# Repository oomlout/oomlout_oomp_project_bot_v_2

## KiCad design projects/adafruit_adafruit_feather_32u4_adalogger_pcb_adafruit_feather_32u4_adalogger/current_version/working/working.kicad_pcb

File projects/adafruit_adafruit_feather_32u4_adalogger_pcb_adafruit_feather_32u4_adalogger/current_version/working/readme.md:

# adafruit_feather_32u4_adalogger_pcb
 
## summary 
* id: adafruit_adafruit_feather_32u4_adalogger_pcb_adafruit_feather_32u4_adalogger
* user: adafruit
* name: adafruit_feather_32u4_adalogger_pcb
* board: adafruit_feather_32u4_adalogger
* repo: https://github.com/adafruit/Adafruit-Feather-32u4-Adalogger-PCB

* src_file_repo_sch: 
* src_file_repo_sch_link: https://github.com/adafruit/Adafruit-Feather-32u4-Adalogger-PCB/tree/master/
* full details link: https://github.com/oomlout/oomlout_oomp_project_bot_v_2/tree/main/projects/adafruit_adafruit_feather_32u4_adalogger_pcb_adafruit_feather_32u4_adalogger/current_version/working  

## schematic  
  
[schematic (pdf)](working_schematic.pdf) 

## pcb  

[board (pdf)](working.pdf)  

## working_bom
| Id | Designator | Footprint | Quantity | Designation | Supplier and ref |  | None | 
| --- | --- | --- | --- | --- | --- | --- | --- | 
| 1 | U$35,U$34 | FIDUCIAL_1MM | 2 | FIDUCIAL" |  |  | [''] | 
| 2 | U3 | SOT23-5 | 1 | MCP73831T-2ACI/OT |  |  | [''] | 
| 3 | U$32,U$31 | MOUNTINGHOLE_2.5_PLATED | 2 | MOUNTINGHOLE2.5 |  |  | [''] | 
| 4 | C7,C14 | 0603-NO | 2 | 1uF |  |  | [''] | 
| 5 | IC1 | TQFN44_7MM | 1 | ATMEGA32U4-MU |  |  | [''] | 
| 6 | C8,C3,C6 | 0805-NO | 3 | 10ÂµF |  |  | [''] | 
| 7 | R8 | 0603-NO | 1 | 10K\ |  |  | [''] | 
| 8 | X1 | JSTPH2 | 1 | JSTPH |  |  | [''] | 
| 9 | R5,R4 | 0603-NO | 2 | 22 |  |  | [''] | 
| 10 | R3,R9 | 0603-NO | 2 | 100k |  |  | [''] | 
| 11 | JP1 | 1X16_ROUND | 1 |  |  |  | [''] | 
| 12 | U$5 | PCBFEAT-REV-040 | 1 |  |  |  | [''] | 
| 13 | C9 | 0805-NO | 1 | 10uF |  |  | [''] | 
| 14 | @HOLE1,@HOLE0 |  | 2 |  |  |  | [''] | 
| 15 | JP3 | 1X12_ROUND | 1 |  |  |  | [''] | 
| 16 | U2 | SOT23-5 | 1 | SPX3819-3.3 |  |  | [''] | 
| 17 | X2 | MICROSD | 1 | microsd |  |  | [''] | 
| 18 | L0 | CHIPLED_0805_NOOUTLINE | 1 | RED |  |  | [''] | 
| 19 | D4 | SOD-123 | 1 | MBR120 |  |  | [''] | 
| 20 | SW1 | KMR2 | 1 | SPST_TACT-KMR2 |  |  | [''] | 
| 21 | R1,R2 | 0603-NO | 2 | 1K |  |  | [''] | 
| 22 | X3 | 4UCONN_20329_V2 | 1 | microUSB |  |  | [''] | 
| 23 | L1 | CHIPLED_0805_NOOUTLINE | 1 | GREEN |  |  | [''] | 
| 24 | R7 | 0603-NO | 1 | 2.2K |  |  | [''] | 
| 25 | Y1 | RESONATOR-SMD | 1 | 8MHz |  |  | [''] | 
| 26 | R6 | _0603MP | 1 | 100K |  |  | [''] | 
| 27 | CHG0 | CHIPLED_0805_NOOUTLINE | 1 | ORANGE |  |  | [''] | 
| 28 | U$7 | ADAFRUIT_3.5MM | 1 |  |  |  | [''] | 
| 29 | U$4 | FEATHERLOGO | 1 |  |  |  | [''] | 
| 30 | U$6 | ADALOGGER_LOGO | 1 |  |  |  | [''] | 

## bom_schematic
| Ref | Qnty | Value | Cmp name | Footprint | Description | Vendor | DNP | 
| --- | --- | --- | --- | --- | --- | --- | --- | 
| C3, C6, C8 | 3 | 10ÂµF | CAP_CERAMIC0805-NOOUTLINE | working:0805-NO |  |  |  | 
| C7, C14 | 2 | 1uF | CAP_CERAMIC0603_NO | working:0603-NO |  |  |  | 
| C9 | 1 | 10uF | CAP_CERAMIC0805-NOOUTLINE | working:0805-NO |  |  |  | 
| CHG0 | 1 | ORANGE | LED0805_NOOUTLINE | working:CHIPLED_0805_NOOUTLINE |  |  |  | 
| D4 | 1 | MBR120 | DIODE-SCHOTTKYSOD-123 | working:SOD-123 |  |  |  | 
| IC1 | 1 | ATMEGA32U4-MU | ATMEGA32U4-MU | working:TQFN44_7MM |  |  |  | 
| JP1 | 1 | HEADER-1X16ROUND | HEADER-1X16ROUND | working:1X16_ROUND |  |  |  | 
| JP3 | 1 | HEADER-1X12 | HEADER-1X12 | working:1X12_ROUND |  |  |  | 
| L0 | 1 | RED | LED0805_NOOUTLINE | working:CHIPLED_0805_NOOUTLINE |  |  |  | 
| L1 | 1 | GREEN | LED0805_NOOUTLINE | working:CHIPLED_0805_NOOUTLINE |  |  |  | 
| R1, R2 | 2 | 1K | RESISTOR_0603_NOOUT | working:0603-NO |  |  |  | 
| R3, R9 | 2 | 100k | RESISTOR_0603_NOOUT | working:0603-NO |  |  |  | 
| R4, R5 | 2 | 22 | RESISTOR_0603_NOOUT | working:0603-NO |  |  |  | 
| R6 | 1 | 100K | RESISTOR_0603MP | working:_0603MP |  |  |  | 
| R7 | 1 | 2.2K | RESISTOR_0603_NOOUT | working:0603-NO |  |  |  | 
| R8 | 1 | 10K\ | RESISTOR_0603_NOOUT | working:0603-NO |  |  |  | 
| SW1 | 1 | SPST_TACT-KMR2 | SPST_TACT-KMR2 | working:KMR2 |  |  |  | 
| U2 | 1 | SPX3819-3.3 | VREG_SOT23-5 | working:SOT23-5 |  |  |  | 
| U3 | 1 | MCP73831T-2ACI/OT | MCP73831/2 | working:SOT23-5 |  |  |  | 
| U$31, U$32 | 2 | MOUNTINGHOLE2.5 | MOUNTINGHOLE2.5 | working:MOUNTINGHOLE_2.5_PLATED |  |  |  | 
| U$34, U$35 | 2 | FIDUCIAL"" | FIDUCIAL{dblquote}{dblquote} | working:FIDUCIAL_1MM |  |  |  | 
| X1 | 1 | JSTPH | CON_JST_PH_2PIN | working:JSTPH2 |  |  |  | 
| X2 | 1 | microsd | MICROSD | working:MICROSD |  |  |  | 
| X3 | 1 | microUSB | USB_MICRO_20329_V2 | working:4UCONN_20329_V2 |  |  |  | 
| Y1 | 1 | RESONATORSMD | RESONATORSMD | working:RESONATOR-SMD |  |  |  | 

## mounting_holes
| x | y | package | value | ref | size | 
| --- | --- | --- | --- | --- | --- | 
| 0.0 | 17.78 | MOUNTINGHOLE_2.5_PLATED | MOUNTINGHOLE2.5 | U$31 | m3 | 
| 0.0 | 0.0 | MOUNTINGHOLE_2.5_PLATED | MOUNTINGHOLE2.5 | U$32 | m3 |

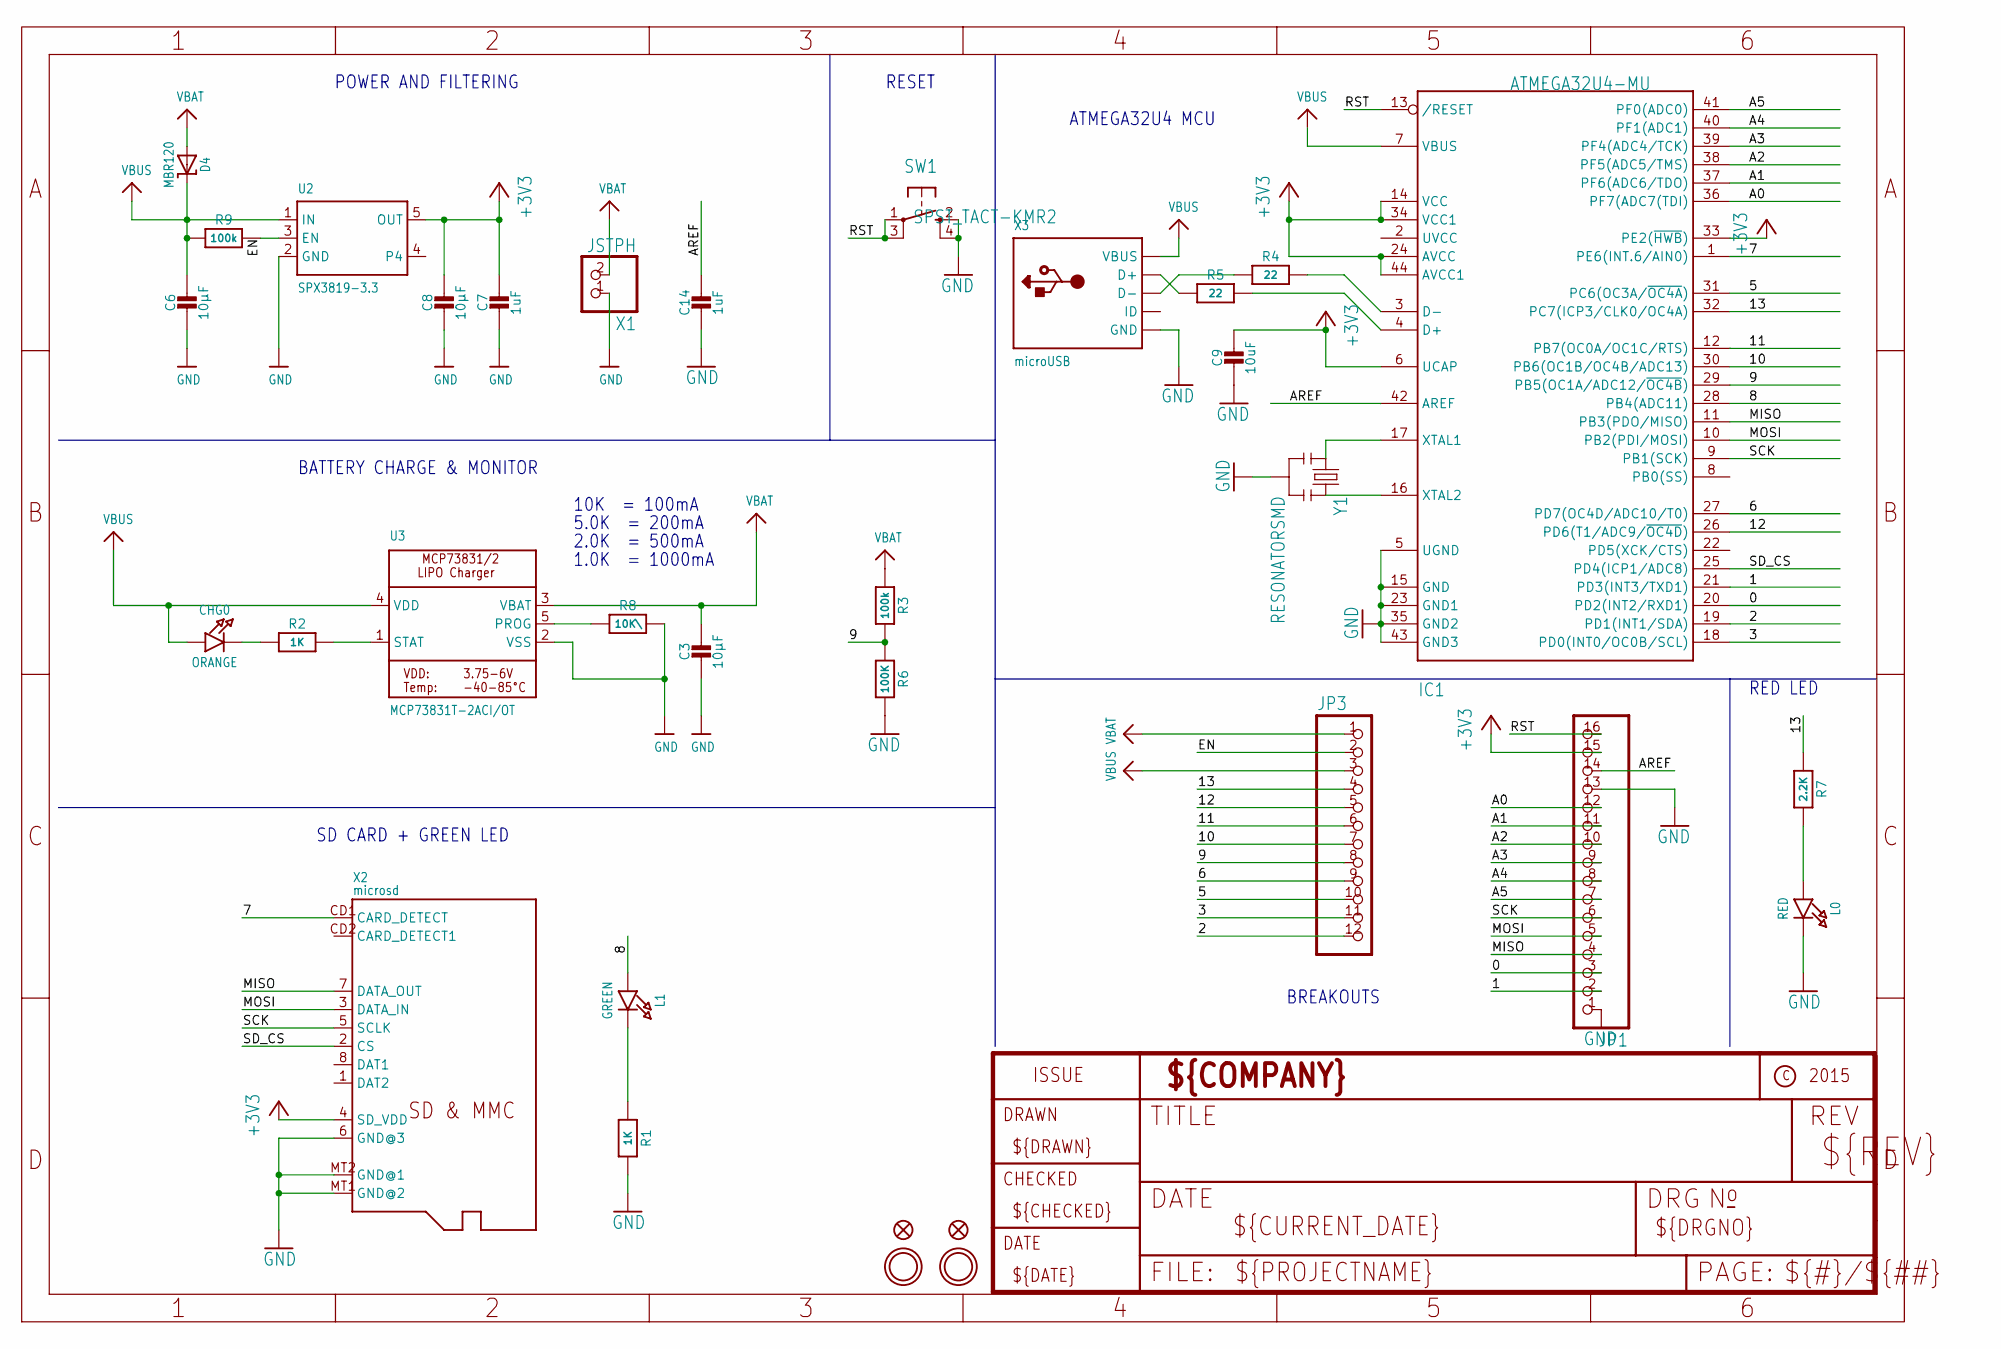
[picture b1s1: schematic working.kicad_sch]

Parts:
C3, C6, C8: 10µF; 0805-NO
C7, C14: 1uF; 0603-NO
C9: 10uF; 0805-NO
CHG0: ORANGE; CHIPLED_0805_NOOUTLINE
D4: MBR120; SOD-123
IC1: ATMEGA32U4-MU; TQFN44_7MM
JP1: HEADER-1X16ROUND; 1X16_ROUND
JP3: HEADER-1X12; 1X12_ROUND
L0: RED; CHIPLED_0805_NOOUTLINE
L1: GREEN; CHIPLED_0805_NOOUTLINE
R1, R2: 1K; 0603-NO
R3, R9: 100k; 0603-NO
R4, R5: 22; 0603-NO
R6: 100K; _0603MP
R7: 2.2K; 0603-NO
R8: 10K\; 0603-NO
SW1: SPST_TACT-KMR2; KMR2
U2: SPX3819-3.3; SOT23-5
U3: MCP73831T-2ACI/OT; SOT23-5
U$31, U$32: MOUNTINGHOLE2.5; MOUNTINGHOLE_2.5_PLATED
U$34, U$35: FIDUCIAL""; FIDUCIAL_1MM
X1: JSTPH; JSTPH2
X2: microsd; MICROSD
X3: microUSB; 4UCONN_20329_V2
Y1: RESONATORSMD; RESONATOR-SMD

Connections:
0: IC1.20 (PD2(INT2/RXD1)), JP1.3
1: IC1.21 (PD3(INT3/TXD1)), JP1.2
2: IC1.19 (PD1(INT1/SDA)), JP3.12
3: IC1.18 (PD0(INT0/OC0B/SCL)), JP3.11
5: IC1.31 (PC6(OC3A/~OC4A)), JP3.10
6: IC1.27 (PD7(OC4D/ADC10/T0)), JP3.9
7: IC1.1 (PE6(INT.6/AIN0)), X2.CD1 (CARD_DETECT)
8: IC1.28 (PB4(ADC11)), L1.A
9: IC1.29 (PB5(OC1A/ADC12/~OC4B)), JP3.8, R3.2, R6.1
10: IC1.30 (PB6(OC1B/OC4B/ADC13)), JP3.7
11: IC1.12 (PB7(OC0A/OC1C/RTS)), JP3.6
12: IC1.26 (PD6(T1/ADC9/~OC4D)), JP3.5
13: IC1.32 (PC7(ICP3/CLK0/OC4A)), JP3.4, R7.1
+3V3: C7.1, C8.1, C9.1, IC1.6 (UCAP), IC1.14 (VCC), IC1.24 (AVCC), IC1.33 (PE2(~HWB)), IC1.34 (VCC1), IC1.44 (AVCC1), JP1.15, U2.5 (OUT), X2.4 (SD_VDD)
A0: IC1.36 (PF7(ADC7(TDI)), JP1.12
A1: IC1.37 (PF6(ADC6/TDO)), JP1.11
A2: IC1.38 (PF5(ADC5/TMS)), JP1.10
A3: IC1.39 (PF4(ADC4/TCK)), JP1.9
A4: IC1.40 (PF1(ADC1)), JP1.8
A5: IC1.41 (PF0(ADC0)), JP1.7
AREF: C14.1, IC1.42 (AREF), JP1.14
D+: IC1.4 (D+), R5.2
D-: IC1.3 (D-), R4.2
EN: JP3.2, R9.2, U2.3 (EN)
GND: C3.2, C6.2, C7.2, C8.2, C9.2, C14.2, IC1.5 (UGND), IC1.15 (GND), IC1.23 (GND1), IC1.35 (GND2), IC1.43 (GND3), JP1.1, JP1.13, L0.C, R1.2, R6.2, R8.2, SW1.2 (S), SW1.4 (S1), U2.2 (GND), U3.2 (VSS), X1.1, X2.6 (GND@3), X2.MT1 (GND@2), X2.MT2 (GND@1), X3.BASE@1 (GND), X3.BASE@2 (GND), X3.GND, X3.SPRT@1 (GND), X3.SPRT@2 (GND), X3.SPRT@3 (GND), X3.SPRT@4 (GND), Y1.2
MISO: IC1.11 (PB3(PDO/MISO)), JP1.4, X2.7 (DATA_OUT)
MOSI: IC1.10 (PB2(PDI/MOSI)), JP1.5, X2.3 (DATA_IN)
unnamed: CHG0.C, R2.1
unnamed: L0.A, R7.2
unnamed: R2.2, U3.1 (STAT)
unnamed: R8.1, U3.5 (PROG)
unnamed: L1.C, R1.1
unnamed: IC1.16 (XTAL2), Y1.3
unnamed: IC1.17 (XTAL1), Y1.1
unnamed: R5.1, X3.D+
unnamed: R4.1, X3.D-
RST: IC1.13 (/RESET), JP1.16, SW1.1, SW1.3 (P1)
SCK: IC1.9 (PB1(SCK)), JP1.6, X2.5 (SCLK)
SD_CS: IC1.25 (PD4(ICP1/ADC8)), X2.2 (CS)
VBAT: C3.1, D4.A, JP3.1, R3.1, U3.3 (VBAT), X1.2
VBUS: C6.1, CHG0.A, D4.C, IC1.7 (VBUS), JP3.3, R9.1, U2.1 (IN), U3.4 (VDD), X3.VBUS

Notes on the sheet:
10K = 100mA
RESET
5.0K = 200mA
BATTERY CHARGE & MONITOR
2.0K = 500mA
SD CARD + GREEN LED
ATMEGA32U4 MCU
1.0K = 1000mA
POWER AND FILTERING
BREAKOUTS
RED LED

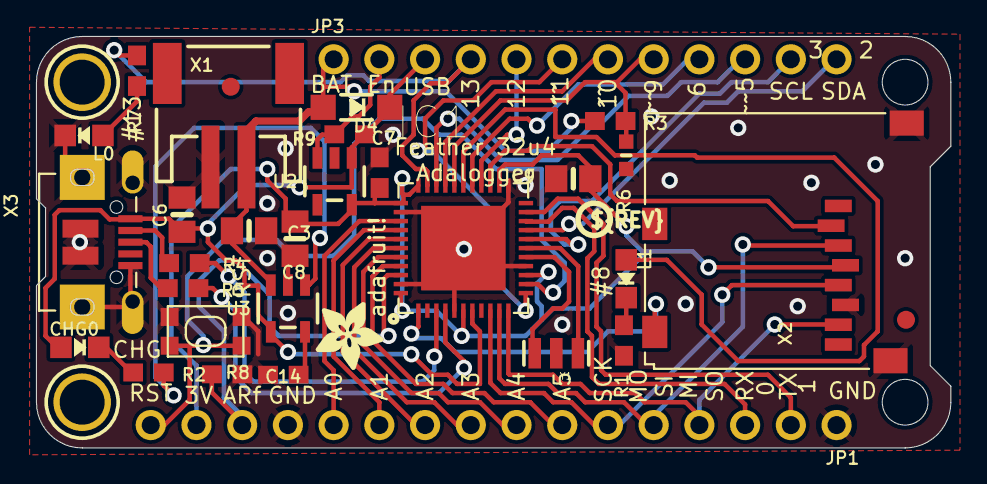
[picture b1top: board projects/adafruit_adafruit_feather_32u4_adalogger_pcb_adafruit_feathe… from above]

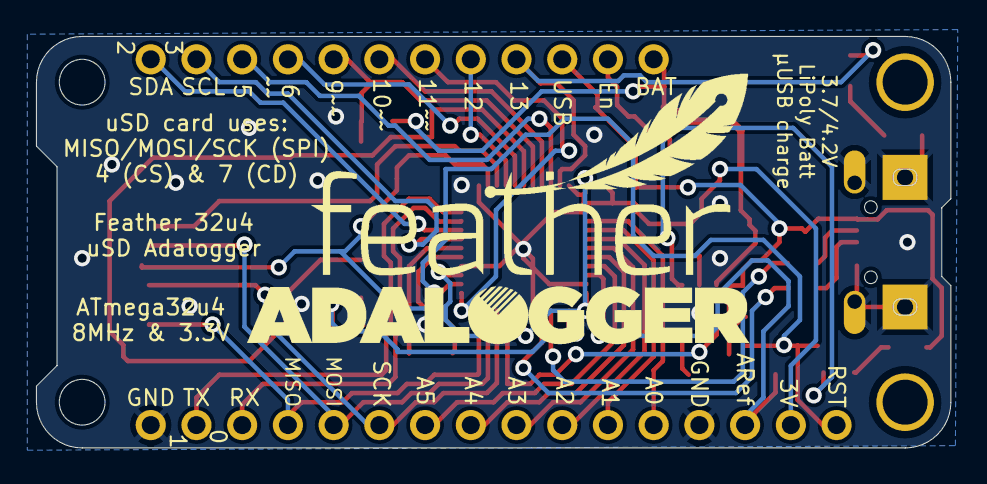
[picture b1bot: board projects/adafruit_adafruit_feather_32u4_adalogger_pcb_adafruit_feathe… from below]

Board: 2 copper layers, 50.8 x 22.9 mm, 39 parts (2 on the bottom side), 41 nets.

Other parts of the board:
@HOLE0, @HOLE1: (no value)
U$4: FEATHERLOGO
U$5: PCBFEAT-REV-040
U$6: ADALOGGER_LOGO
U$7: ADAFRUIT_3.5MM

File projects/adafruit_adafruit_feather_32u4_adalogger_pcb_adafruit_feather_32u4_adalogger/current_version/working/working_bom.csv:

"Id";"Designator";"Footprint";"Quantity";"Designation";"Supplier and ref";
1;"U$35,U$34";"FIDUCIAL_1MM";2;"FIDUCIAL""";;;
2;"U3";"SOT23-5";1;"MCP73831T-2ACI/OT";;;
3;"U$32,U$31";"MOUNTINGHOLE_2.5_PLATED";2;"MOUNTINGHOLE2.5";;;
4;"C7,C14";"0603-NO";2;"1uF";;;
5;"IC1";"TQFN44_7MM";1;"ATMEGA32U4-MU";;;
6;"C8,C3,C6";"0805-NO";3;"10µF";;;
7;"R8";"0603-NO";1;"10K\";;;
8;"X1";"JSTPH2";1;"JSTPH";;;
9;"R5,R4";"0603-NO";2;"22";;;
10;"R3,R9";"0603-NO";2;"100k";;;
11;"JP1";"1X16_ROUND";1;"";;;
12;"U$5";"PCBFEAT-REV-040";1;"";;;
13;"C9";"0805-NO";1;"10uF";;;
14;"@HOLE1,@HOLE0";"";2;"";;;
15;"JP3";"1X12_ROUND";1;"";;;
16;"U2";"SOT23-5";1;"SPX3819-3.3";;;
17;"X2";"MICROSD";1;"microsd";;;
18;"L0";"CHIPLED_0805_NOOUTLINE";1;"RED";;;
19;"D4";"SOD-123";1;"MBR120";;;
20;"SW1";"KMR2";1;"SPST_TACT-KMR2";;;
21;"R1,R2";"0603-NO";2;"1K";;;
22;"X3";"4UCONN_20329_V2";1;"microUSB";;;
23;"L1";"CHIPLED_0805_NOOUTLINE";1;"GREEN";;;
24;"R7";"0603-NO";1;"2.2K";;;
25;"Y1";"RESONATOR-SMD";1;"8MHz";;;
26;"R6";"_0603MP";1;"100K";;;
27;"CHG0";"CHIPLED_0805_NOOUTLINE";1;"ORANGE";;;
28;"U$7";"ADAFRUIT_3.5MM";1;"";;;
29;"U$4";"FEATHERLOGO";1;"";;;
30;"U$6";"ADALOGGER_LOGO";1;"";;;

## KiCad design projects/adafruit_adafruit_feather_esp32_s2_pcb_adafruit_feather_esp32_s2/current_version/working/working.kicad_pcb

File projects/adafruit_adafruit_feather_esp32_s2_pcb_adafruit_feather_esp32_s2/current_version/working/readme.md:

# adafruit_feather_esp32_s2_pcb
 
## summary 
* id: adafruit_adafruit_feather_esp32_s2_pcb_adafruit_feather_esp32_s2
* user: adafruit
* name: adafruit_feather_esp32_s2_pcb
* board: adafruit_feather_esp32_s2
* repo: https://github.com/adafruit/Adafruit-Feather-ESP32-S2-PCB

* src_file_repo_sch: 
* src_file_repo_sch_link: https://github.com/adafruit/Adafruit-Feather-ESP32-S2-PCB/tree/main/
* full details link: https://github.com/oomlout/oomlout_oomp_project_bot_v_2/tree/main/projects/adafruit_adafruit_feather_esp32_s2_pcb_adafruit_feather_esp32_s2/current_version/working  

## schematic  
  
[schematic (pdf)](working_schematic.pdf) 

## pcb  

[board (pdf)](working.pdf)  

## working_bom
| Id | Designator | Footprint | Quantity | Designation | Supplier and ref |  | None | 
| --- | --- | --- | --- | --- | --- | --- | --- | 
| 1 | U$35,U$34 | FIDUCIAL_1MM | 2 | FIDUCIAL_1MM |  |  | [''] | 
| 2 | C2,C9,C7,C1 | 0805-NO | 4 | 10uF |  |  | [''] | 
| 3 | C10,C4,C5 | 0603-NO | 3 | 1uF |  |  | [''] | 
| 4 | D4 | SOD-123 | 1 | MBR540 |  |  | [''] | 
| 5 | X3 | USB_C_CUSB31-CFM2AX-01-X | 1 | USB C |  |  | [''] | 
| 6 | R8,R10,R4,R2,R5,R1 | 0603-NO | 6 | 5.1K |  |  | [''] | 
| 7 | Q3 | SOT23-R | 1 | DMG3415U |  |  | [''] | 
| 8 | U4 | BME280 | 1 | BME280 |  |  | [''] | 
| 9 | C8,C3,C6 | 0805-NO | 3 | 10ÂµF |  |  | [''] | 
| 10 | R3 | RESPACK_4X0603 | 1 | 10K |  |  | [''] | 
| 11 | R7,R12 | 0603-NO | 2 | 100K |  |  | [''] | 
| 12 | U$32,U$31 | MOUNTINGHOLE_2.5_PLATED | 2 | MOUNTINGHOLE2.5 |  |  | [''] | 
| 13 | D3 | CHIPLED_0603_NOOUTLINE | 1 | RED |  |  | [''] | 
| 14 | SW2,SW1 | BTN_KMR2_4.6X2.8 | 2 | KMR2 |  |  | [''] | 
| 15 | U3 | SOT23-5 | 1 | MCP73831T-2ACI/OT |  |  | [''] | 
| 16 | R17 | 0603-NO | 1 | 1Meg |  |  | [''] | 
| 17 | CHG0 | CHIPLED_0603_NOOUTLINE | 1 | ORANGE |  |  | [''] | 
| 18 | LED1 | SK6805_1515 | 1 | WS2812B_SK6805_1515 |  |  | [''] | 
| 19 | X1 | JSTPH2_BATT | 1 | JSTPH |  |  | [''] | 
| 20 | U1 | QFN60_ESP32-S2-MINI-1_EXP | 1 | ESP32-S2-MODULE_MINI |  |  | [''] | 
| 21 | JP1 | 1X16_ROUND | 1 |  |  |  | [''] | 
| 22 | CONN1 | JST_SH4_RA | 1 | JST SH |  |  | [''] | 
| 23 | @HOLE1,@HOLE0 |  | 2 |  |  |  | [''] | 
| 24 | JP3 | 1X12_ROUND | 1 |  |  |  | [''] | 
| 25 | IC1 | WLCSP9 | 1 | LC709203F/MH |  |  | [''] | 
| 26 | U2,U5 | SOT23-5 | 2 | AP2112/RT9080-3.3 |  |  | [''] | 
| 27 | C11 | _0805MP | 1 | 10uF |  |  | [''] | 
| 28 | TP1 | TESTPOINT_ROUND_1.5MM_NO | 1 |  |  |  | [''] | 
| 29 | U$53 | STEMMAQT | 1 |  |  |  | [''] | 
| 30 | U$15 | FEATHERLOGO_MED | 1 |  |  |  | [''] | 
| 31 | U$14 | PCBFEAT-REV-040 | 1 |  |  |  | [''] | 

## bom_schematic
| Ref | Qnty | Value | Cmp name | Footprint | Description | Vendor | DNP | 
| --- | --- | --- | --- | --- | --- | --- | --- | 
| C1, C2, C7, C9 | 4 | 10uF | CAP_CERAMIC0805-NOOUTLINE | working:0805-NO |  |  |  | 
| C3, C6, C8 | 3 | 10ÂµF | CAP_CERAMIC0805-NOOUTLINE | working:0805-NO |  |  |  | 
| C4, C5, C10 | 3 | 1uF | CAP_CERAMIC0603_NO | working:0603-NO |  |  |  | 
| C11 | 1 | 10uF | CAP_CERAMIC_0805MP | working:_0805MP |  |  |  | 
| CHG0 | 1 | ORANGE | LED0603_NOOUTLINE | working:CHIPLED_0603_NOOUTLINE |  |  |  | 
| CONN1 | 1 | STEMMA_I2C_QTRA | STEMMA_I2C_QTRA | working:JST_SH4_RA |  |  |  | 
| D3 | 1 | RED | LED0603_NOOUTLINE | working:CHIPLED_0603_NOOUTLINE |  |  |  | 
| D4 | 1 | MBR540 | DIODE-SCHOTTKYSOD-123 | working:SOD-123 |  |  |  | 
| IC1 | 1 | LC709203F/MH | LC709203F/MH | working:WLCSP9 |  |  |  | 
| JP1 | 1 | HEADER-1X16ROUND | HEADER-1X16ROUND | working:1X16_ROUND |  |  |  | 
| JP3 | 1 | HEADER-1X12 | HEADER-1X12 | working:1X12_ROUND |  |  |  | 
| LED1 | 1 | WS2812B_SK6805_1515 | WS2812B_SK6805_1515 | working:SK6805_1515 |  |  |  | 
| Q3 | 1 | DMG3415U | MOSFET-P | working:SOT23-R |  |  |  | 
| R1, R2, R4, R5, R8, R10 | 6 | 5.1K | RESISTOR_0603_NOOUT | working:0603-NO |  |  |  | 
| R3 | 1 | 10K | RESISTOR_4PACK | working:RESPACK_4X0603 |  |  |  | 
| R7, R12 | 2 | 100K | RESISTOR_0603_NOOUT | working:0603-NO |  |  |  | 
| R17 | 1 | 1Meg | RESISTOR_0603_NOOUT | working:0603-NO |  |  |  | 
| SW1, SW2 | 2 | KMR2 | SWITCH_TACT_SMT4.6X2.8 | working:BTN_KMR2_4.6X2.8 |  |  |  | 
| TP1 | 1 | TESTPOINTROUND1.5MMNO | TESTPOINTROUND1.5MMNO | working:TESTPOINT_ROUND_1.5MM_NO |  |  |  | 
| U1 | 1 | ESP32-S2-MODULE_MINI | ESP32-S2-MODULE_MINI | working:QFN60_ESP32-S2-MINI-1_EXP |  |  |  | 
| U2, U5 | 2 | AP2112/RT9080-3.3 | VREG_SOT23-5 | working:SOT23-5 |  |  |  | 
| U3 | 1 | MCP73831T-2ACI/OT | MCP73831/2 | working:SOT23-5 |  |  |  | 
| U4 | 1 | BME280 | BME280 | working:BME280 |  |  |  | 
| U$31, U$32 | 2 | MOUNTINGHOLE2.5 | MOUNTINGHOLE2.5 | working:MOUNTINGHOLE_2.5_PLATED |  |  |  | 
| U$34, U$35 | 2 | FIDUCIAL_1MM | FIDUCIAL_1MM | working:FIDUCIAL_1MM |  |  |  | 
| X1 | 1 | CON_JST_PH_2PIN_MT_BATT | CON_JST_PH_2PIN_MT_BATT | working:JSTPH2_BATT |  |  |  | 
| X3 | 1 | USB C | USB_C | working:USB_C_CUSB31-CFM2AX-01-X |  |  |  | 

## mounting_holes
| x | y | package | value | ref | size | 
| --- | --- | --- | --- | --- | --- | 
| 0.0 | 17.78 | MOUNTINGHOLE_2.5_PLATED | MOUNTINGHOLE2.5 | U$31 | m3 | 
| 0.0 | 0.0 | MOUNTINGHOLE_2.5_PLATED | MOUNTINGHOLE2.5 | U$32 | m3 |

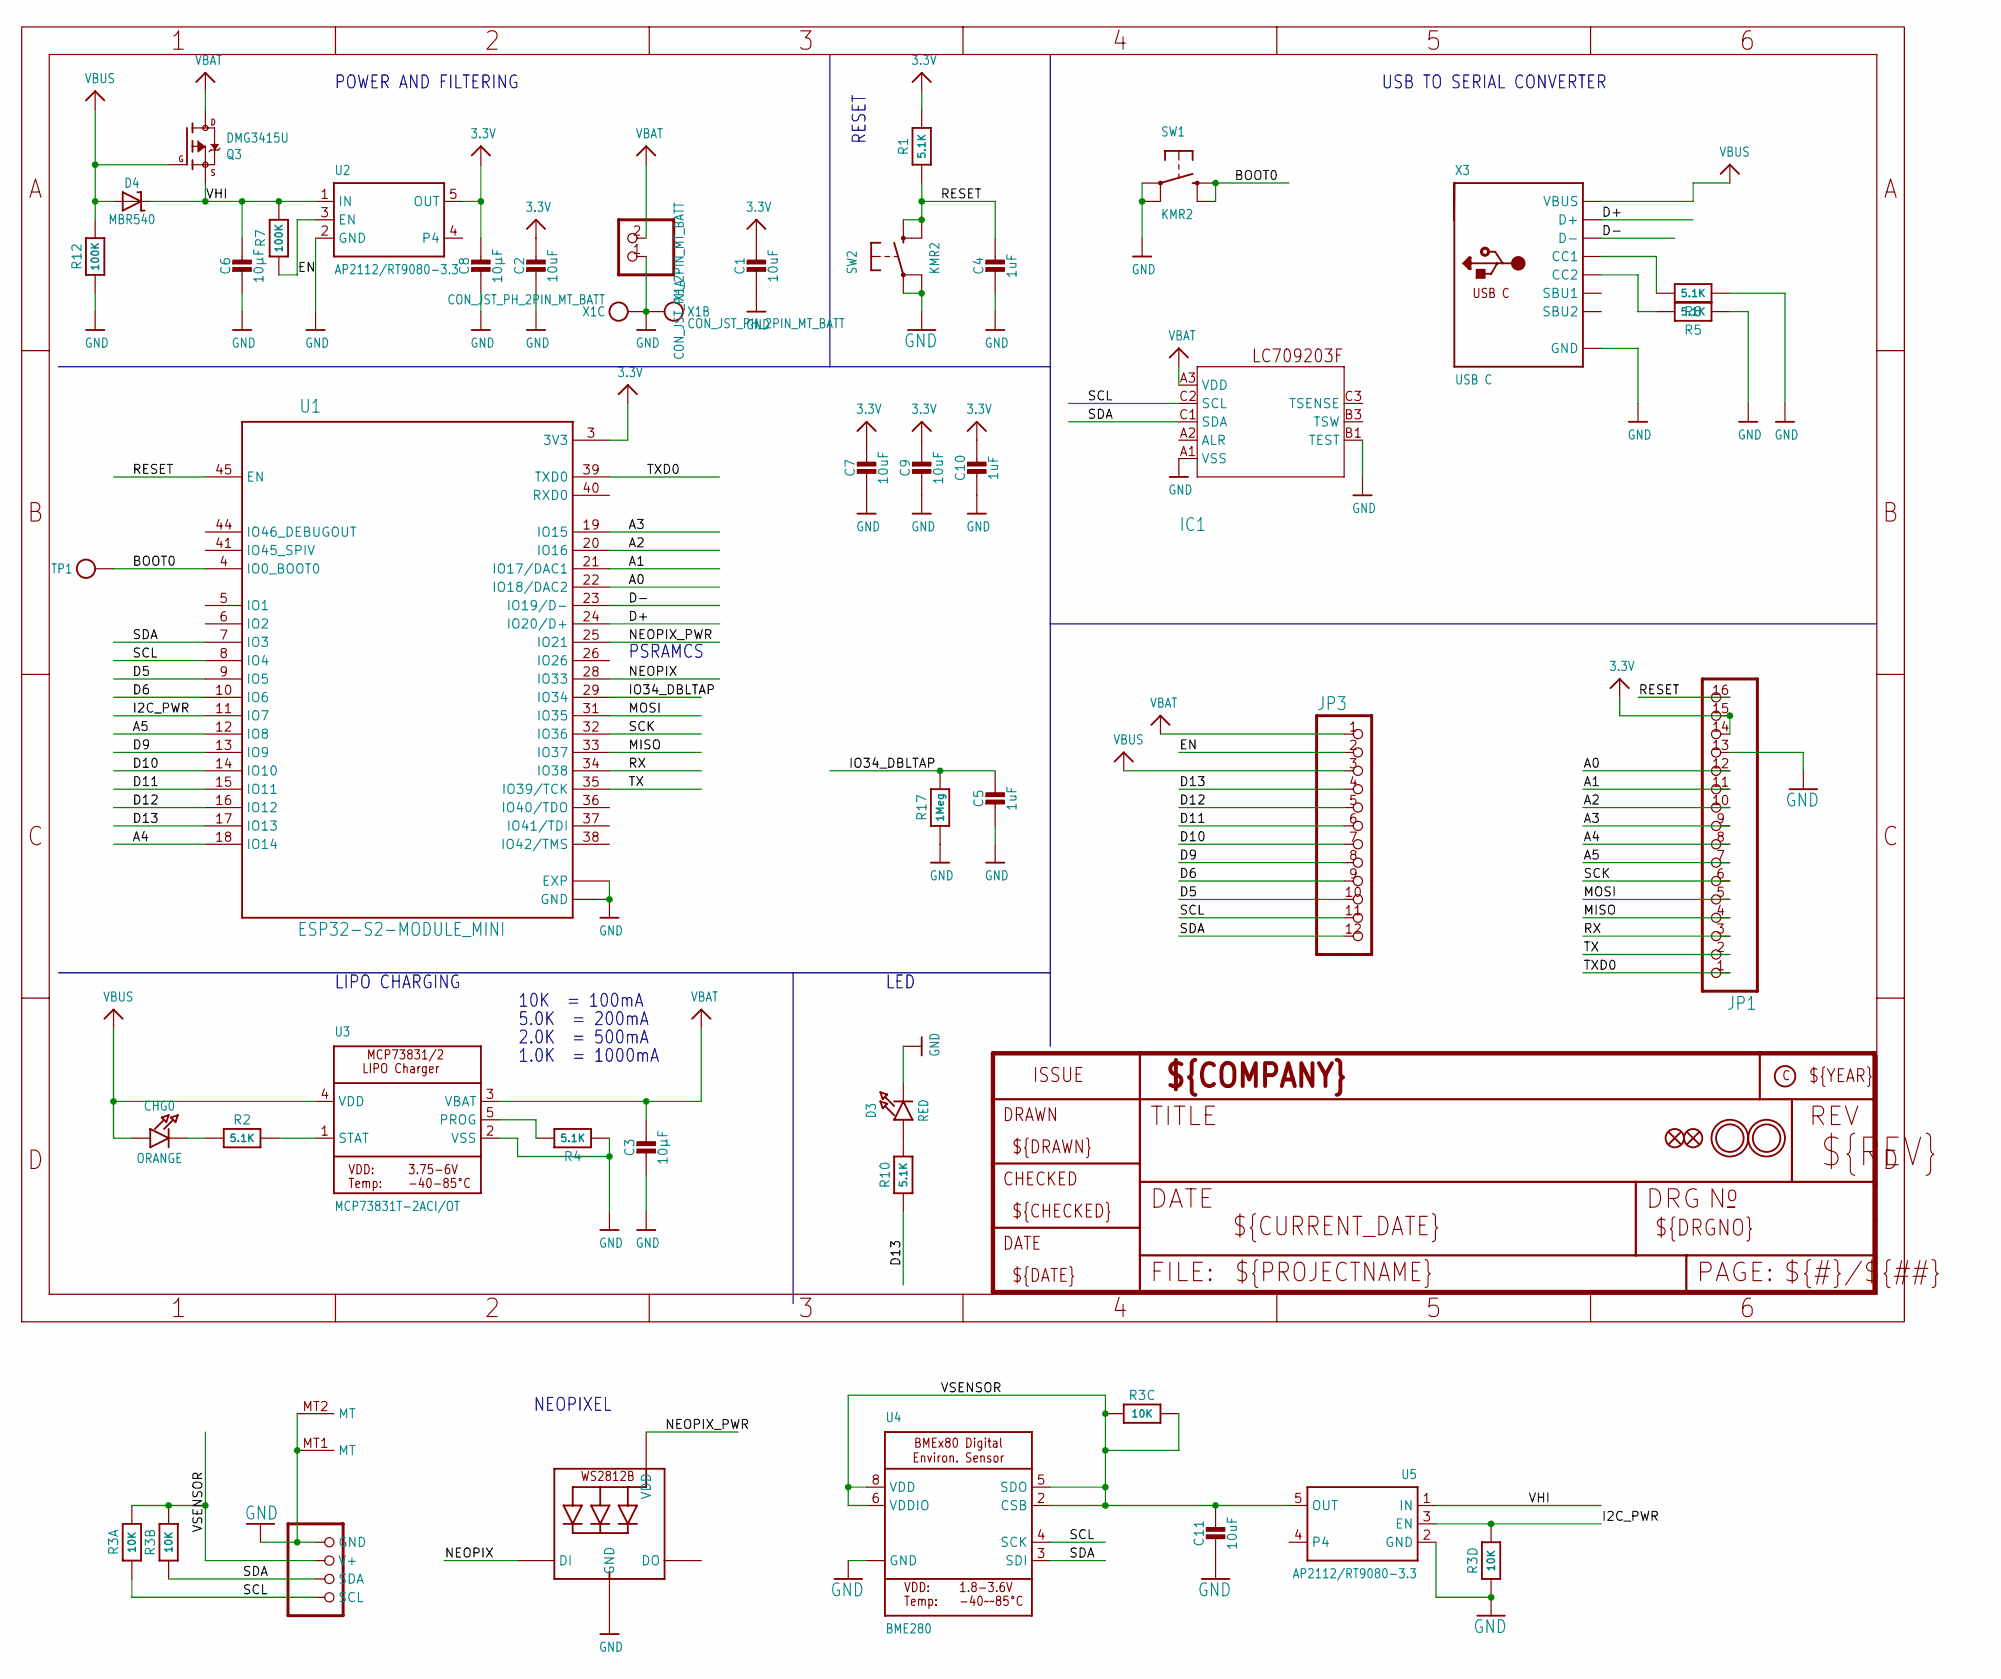
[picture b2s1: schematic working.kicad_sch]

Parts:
C1, C2, C7, C9: 10uF; 0805-NO
C3, C6, C8: 10µF; 0805-NO
C4, C5, C10: 1uF; 0603-NO
C11: 10uF; _0805MP
CHG0: ORANGE; CHIPLED_0603_NOOUTLINE
CONN1: STEMMA_I2C_QTRA; JST_SH4_RA
D3: RED; CHIPLED_0603_NOOUTLINE
D4: MBR540; SOD-123
IC1: LC709203F/MH; WLCSP9
JP1: HEADER-1X16ROUND; 1X16_ROUND
JP3: HEADER-1X12; 1X12_ROUND
LED1: WS2812B_SK6805_1515; SK6805_1515
Q3: DMG3415U; SOT23-R
R1, R2, R4, R5, R8, R10: 5.1K; 0603-NO
R3: 10K; RESPACK_4X0603
R7, R12: 100K; 0603-NO
R17: 1Meg; 0603-NO
SW1, SW2: KMR2; BTN_KMR2_4.6X2.8
TP1: TESTPOINTROUND1.5MMNO; TESTPOINT_ROUND_1.5MM_NO
U1: ESP32-S2-MODULE_MINI; QFN60_ESP32-S2-MINI-1_EXP
U2, U5: AP2112/RT9080-3.3; SOT23-5
U3: MCP73831T-2ACI/OT; SOT23-5
U4: BME280
U$31, U$32: MOUNTINGHOLE2.5; MOUNTINGHOLE_2.5_PLATED
U$34, U$35: FIDUCIAL_1MM
X1: CON_JST_PH_2PIN_MT_BATT; JSTPH2_BATT
X3: USB C; USB_C_CUSB31-CFM2AX-01-X

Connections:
3.3V: C1.1, C2.1, C7.1, C8.1, C9.1, C10.1, JP1.14, JP1.15, R1.2, U1.3 (3V3), U2.5 (OUT)
A0: JP1.12, U1.22 (IO18/DAC2)
A1: JP1.11, U1.21 (IO17/DAC1)
A2: JP1.10, U1.20 (IO16)
A3: JP1.9, U1.19 (IO15)
A4: JP1.8, U1.18 (IO14)
A5: JP1.7, U1.12 (IO8)
BOOT0: SW1.B (S), SW1.B' (S1), TP1.P$1, U1.4 (IO0_BOOT0)
D5: JP3.10, U1.9 (IO5)
D6: JP3.9, U1.10 (IO6)
D9: JP3.8, U1.13 (IO9)
D10: JP3.7, U1.14 (IO10)
D11: JP3.6, U1.15 (IO11)
D12: JP3.5, U1.16 (IO12)
D13: JP3.4, R10.1, U1.17 (IO13)
D+: U1.24 (IO20/D+), X3.A6 (D+), X3.B6 (D+)
D-: U1.23 (IO19/D-), X3.A7 (D-), X3.B7 (D-)
EN: JP3.2, R7.1, U2.3 (EN)
GND: C1.2, C2.2, C3.2, C4.2, C5.2, C6.2, C7.2, C8.2, C9.2, C10.2, C11.2, CONN1.1 (GND), CONN1.MT1 (MT), CONN1.MT2 (MT), D3.C, IC1.A1 (VSS), IC1.B1 (TEST), JP1.13, LED1.4 (GND), R3.4 (1), R4.1, R5.1, R8.1, R12.1, R17.1, SW1.A, SW1.A' (P1), SW2.A, SW2.A' (P1), U1.1 (GND), U1.2 (GND), U1.30 (GND), U1.42 (GND), U1.43 (GND), U1.46 (GND), U1.47 (GND), U1.48 (GND), U1.49 (GND), U1.50 (GND), U1.51 (GND), U1.52 (GND), U1.53 (GND), U1.54 (GND), U1.55 (GND), U1.56 (GND), U1.57 (GND), U1.58 (GND), U1.59 (GND), U1.60 (GND), U1.61 (EXP), U1.62 (EXP), U1.63 (EXP), U1.64 (EXP), U1.65 (EXP), U1.66 (EXP), U1.67 (EXP), U1.68 (EXP), U1.69 (EXP), U1.70 (EXP), U1.71 (EXP), U1.72 (EXP), U1.73 (EXP), U2.2 (GND), U3.2 (VSS), U4.1 (GND), U4.7 (GND), U5.2 (GND), X1.1, X1.NC1, X1.NC2, X3.A1B12 (GND), X3.B1A12 (GND)
I2C_PWR: R3.5 (2), U1.11 (IO7), U5.3 (EN)
IO34_DBLTAP: C5.1, R17.2, U1.29 (IO34)
MISO: JP1.4, U1.33 (IO37)
MOSI: JP1.5, U1.31 (IO35)
unnamed: CHG0.C, R2.1
unnamed: R2.2, U3.1 (STAT)
unnamed: R4.2, U3.5 (PROG)
unnamed: D3.A, R10.2
unnamed: R8.2, X3.A5 (CC1)
unnamed: R5.2, X3.B5 (CC2)
NEOPIX: LED1.1 (DI), U1.28 (IO33)
NEOPIX_PWR: LED1.2 (VDD), U1.25 (IO21)
RESET: C4.1, JP1.16, R1.1, SW2.B (S), SW2.B' (S1), U1.45 (EN)
RX: JP1.3, U1.34 (IO38)
SCK: JP1.6, U1.32 (IO36)
SCL: CONN1.4 (SCL), IC1.C2 (SCL), JP3.11, R3.1, U1.8 (IO4), U4.4 (SCK)
SDA: CONN1.3 (SDA), IC1.C1 (SDA), JP3.12, R3.2 (1), U1.7 (IO3), U4.3 (SDI)
TX: JP1.2, U1.35 (IO39/TCK)
TXD0: JP1.1, U1.39 (TXD0)
VBAT: C3.1, IC1.A3 (VDD), JP3.1, Q3.3 (D), U3.3 (VBAT), X1.2
VBUS: CHG0.A, D4.A, JP3.3, Q3.1 (G), R12.2, U3.4 (VDD), X3.A4B9 (VBUS), X3.B4A9 (VBUS)
VHI: C6.1, D4.C, Q3.2 (S), R7.2, U2.1 (IN), U5.1 (IN)
VSENSOR: C11.1, CONN1.2 (V+), R3.3 (1), R3.6 (2), R3.7 (2), R3.8 (2), U4.2 (CSB), U4.5 (SDO), U4.6 (VDDIO), U4.8 (VDD), U5.5 (OUT)

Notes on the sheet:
2.0K = 500mA
1.0K = 1000mA
LIPO CHARGING
NEOPIXEL
PSRAMCS
POWER AND FILTERING
LED
5.0K = 200mA
RESET
10K = 100mA
USB TO SERIAL CONVERTER

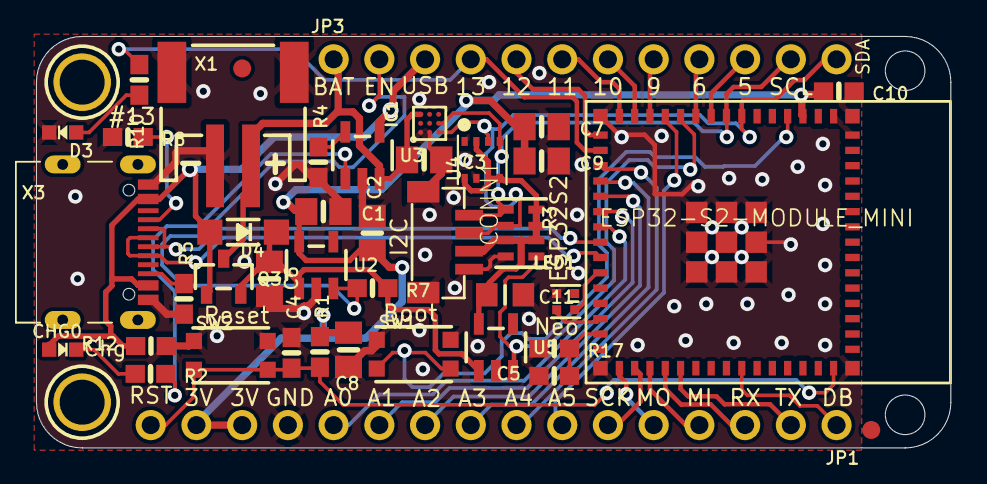
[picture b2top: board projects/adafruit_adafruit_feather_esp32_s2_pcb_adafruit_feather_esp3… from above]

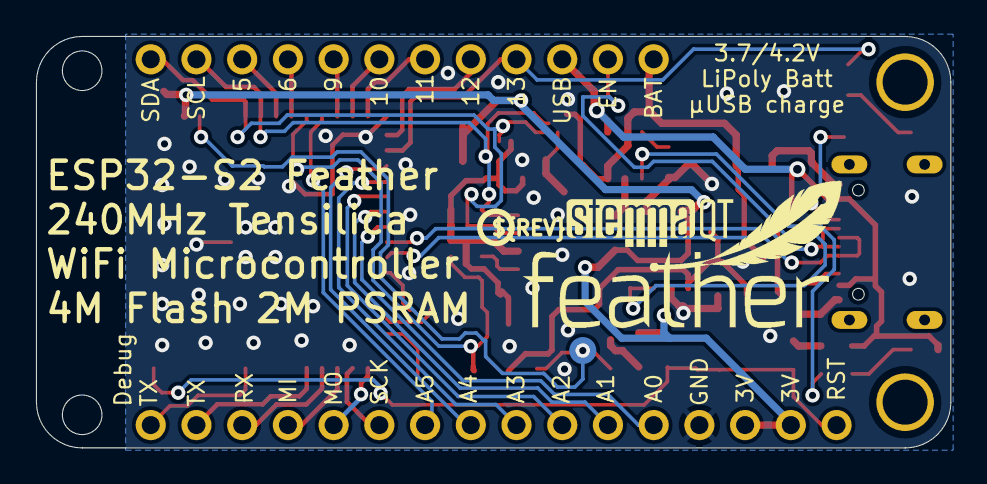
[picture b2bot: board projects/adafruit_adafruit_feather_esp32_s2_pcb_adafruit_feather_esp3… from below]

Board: 2 copper layers, 50.8 x 22.9 mm, 49 parts (4 on the bottom side), 42 nets.

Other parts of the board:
@HOLE0, @HOLE1: (no value)
U$14: PCBFEAT-REV-040
U$15: FEATHERLOGO_MED
U$53: STEMMAQT
